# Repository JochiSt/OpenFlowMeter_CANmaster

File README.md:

# OpenFlowMeter_CANmaster
 CAN Bus Master for OpenFlowMeter

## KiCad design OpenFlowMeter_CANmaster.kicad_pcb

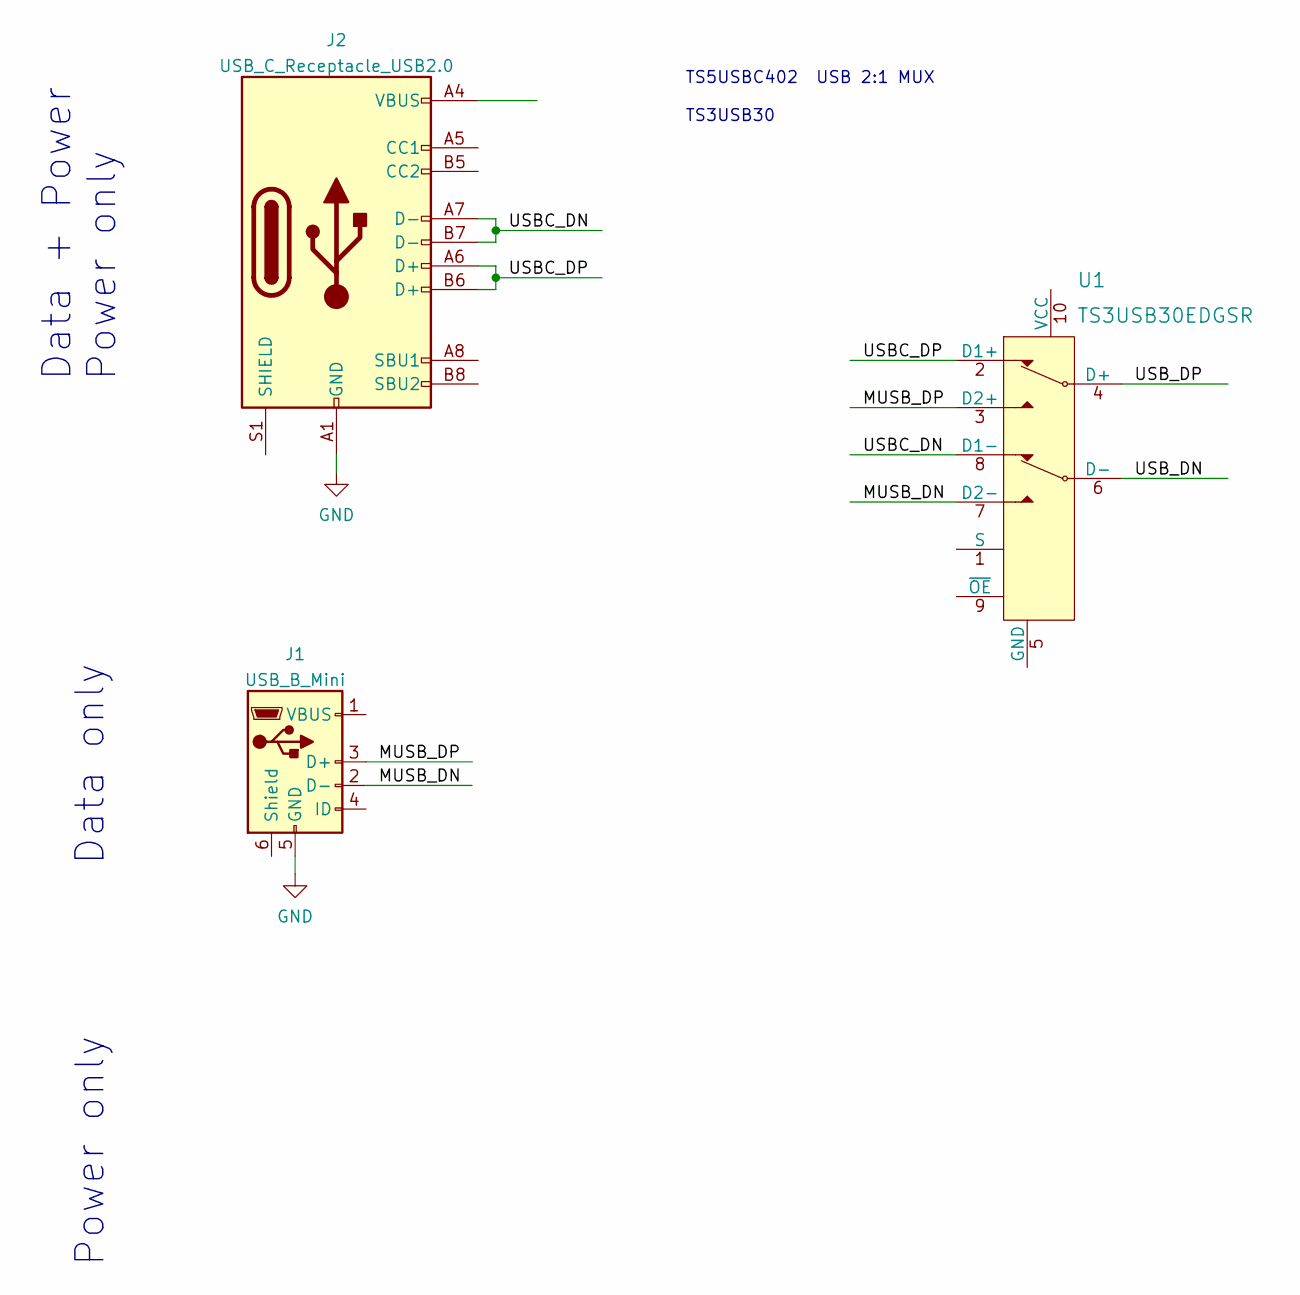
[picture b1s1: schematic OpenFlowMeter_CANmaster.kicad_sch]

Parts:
J1: USB_B_Mini; USB_Mini-B_Wuerth_65100516121_Horizontal
J2: USB_C_Receptacle_USB2.0; USB_C_Receptacle_XKB_U262-16XN-4BVC11
U1: TS3USB30EDGSR; MSOP-10_W3mm; MPN TS3USB30EDGSR; Digi-Key_PN 296-25495-1-ND

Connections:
/MUSB_DN: J1.2 (D-), U1.7 (D2-)
/MUSB_DP: J1.3 (D+), U1.3 (D2+)
/USBC_DN: J2.A7 (D-), J2.B7 (D-), U1.8 (D1-)
/USBC_DP: J2.A6 (D+), J2.B6 (D+), U1.2 (D1+)
/USB_DN: U1.6 (D-)
/USB_DP: U1.4 (D+)
GND: J1.5 (GND), J2.A1 (GND), J2.A12 (GND), J2.B1 (GND), J2.B12 (GND)
unnamed: J2.A4 (VBUS), J2.A9 (VBUS), J2.B4 (VBUS), J2.B9 (VBUS)

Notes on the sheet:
Data + Power Power only
Power only
TS5USBC402 USB 2:1 MUX TS3USB30
Data only

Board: 2 copper layers, 3 parts (0 on the bottom side), 6 nets, no tracks yet.

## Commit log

2022-02-15 ignore zip files
2022-02-15 added 3D model of Housing
2022-12-04 started with CAN Busmaster for OpenFlowMeter
    not much structure in this schematic, just the USB connections and a USB MUX
